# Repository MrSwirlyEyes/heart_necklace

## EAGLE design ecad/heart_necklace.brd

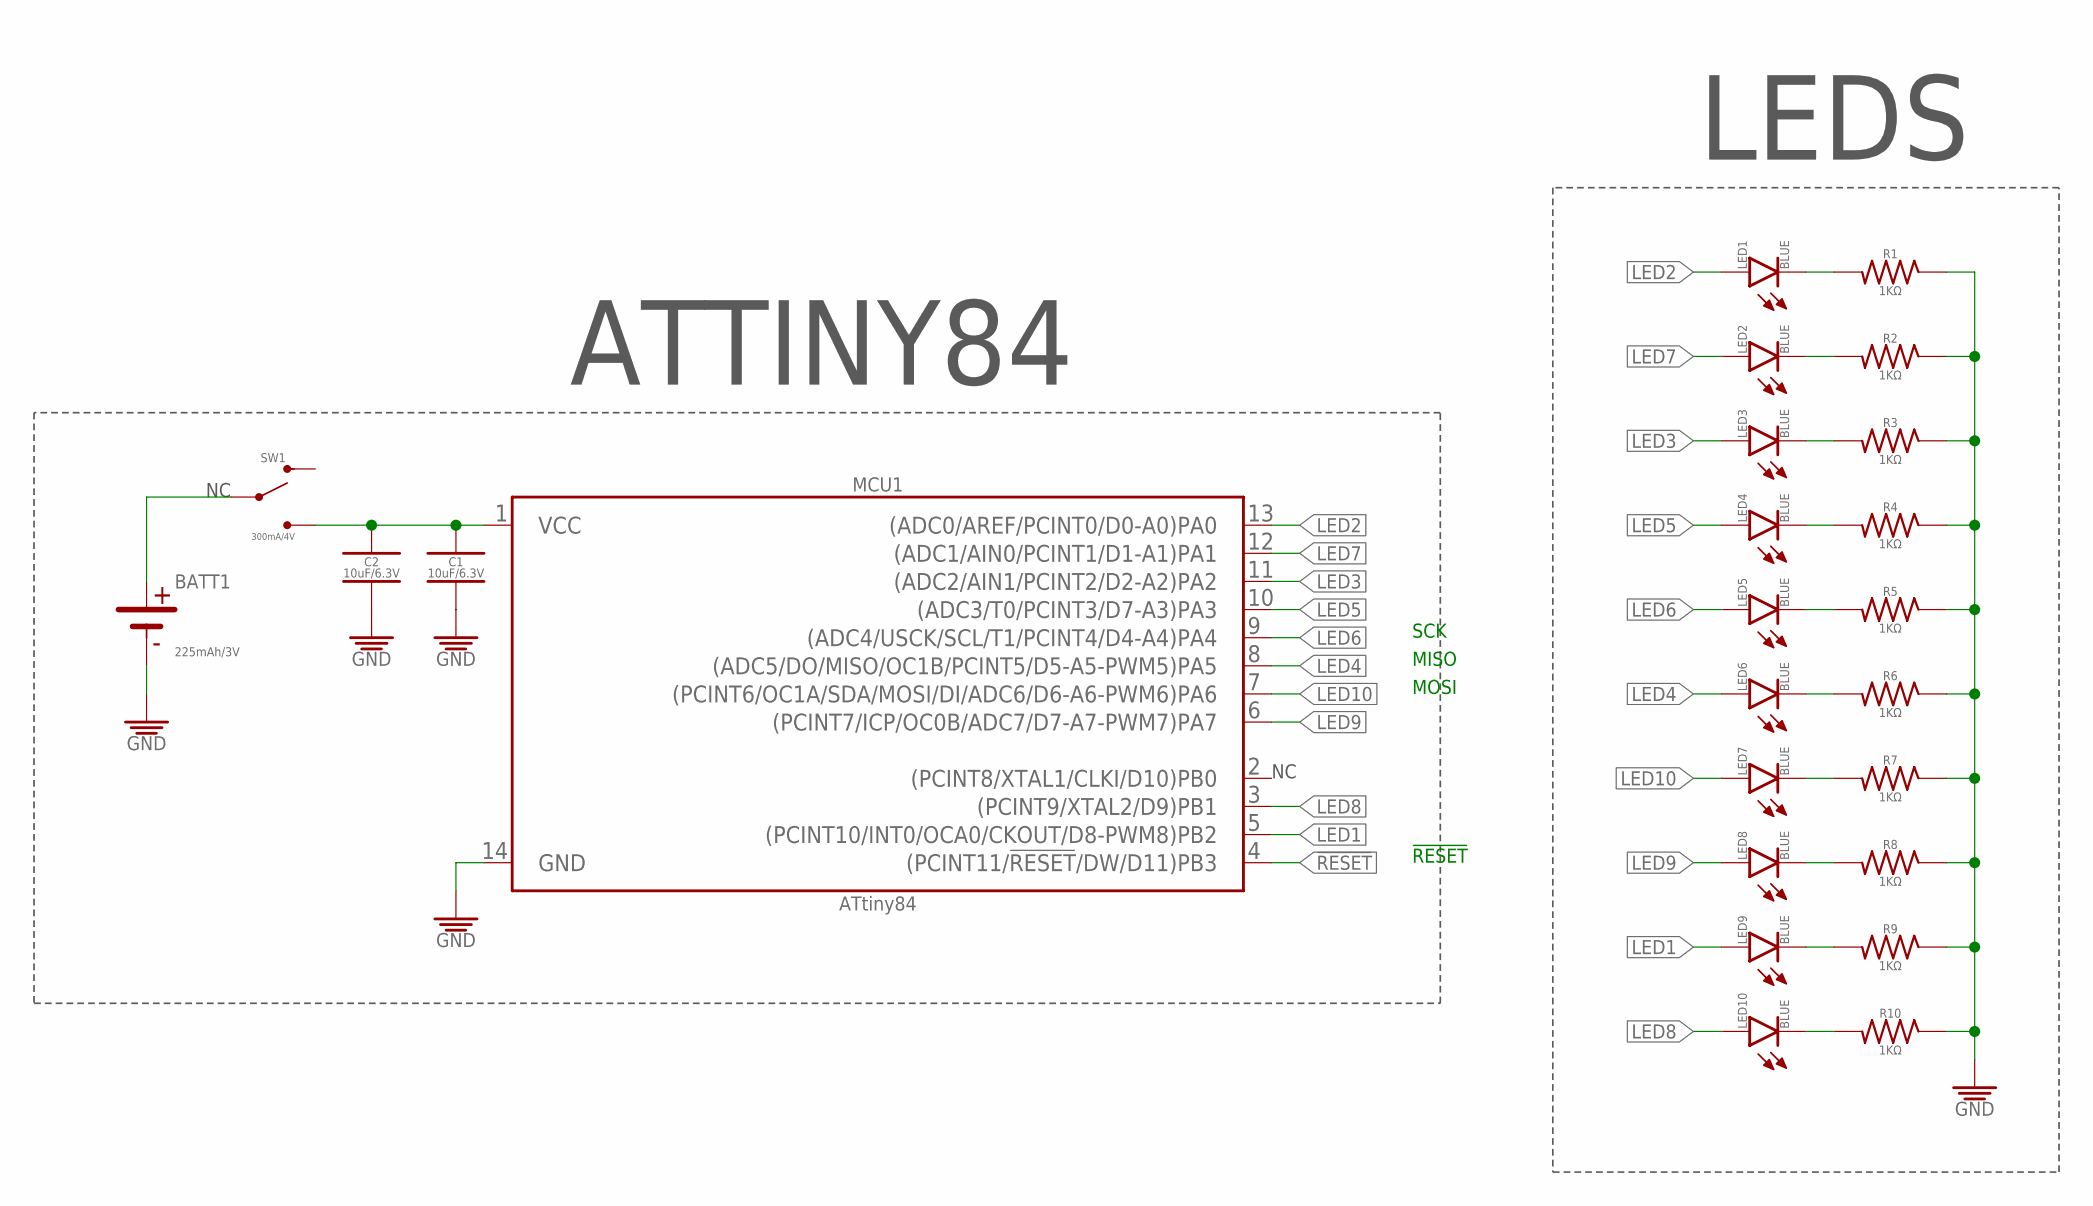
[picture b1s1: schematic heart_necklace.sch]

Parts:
BATT1: 225mAh/3V; CR-2032
C1, C2: 10uF/6.3V; CAPC1005X55_SMD-0402
LED1, LED2, LED3, LED4, LED5, LED6, LED7, LED8, LED9, LED10: BLUE; LEDC2012X120
MCU1: ATtiny84; SOIC127P599X175-14_SOIC-14_NO-SILK
R1, R2, R3, R4, R5, R6, R7, R8, R9, R10: 1KΩ; RESISTOR_SMD-805
SW1: 300mA/4V; SW_SLIDE_SPDT_RA_SMD_4V_300MA_6.7L-2.6W

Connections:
!RESET: MCU1.4 ((PCINT11/!RESET!/DW/D11)PB3)
GND: BATT1.-, C1.2, C2.2, MCU1.14 (GND), R1.1, R2.1, R3.1, R4.1, R5.1, R6.1, R7.1, R8.1, R9.1, R10.1
LED1: LED9.A, MCU1.5 ((PCINT10/INT0/OCA0/CKOUT/D8-PWM8)PB2)
LED2: LED1.A, MCU1.13 ((ADC0/AREF/PCINT0/D0-A0)PA0)
LED3: LED3.A, MCU1.11 ((ADC2/AIN1/PCINT2/D2-A2)PA2)
LED4: LED6.A, MCU1.8 ((ADC5/DO/MISO/OC1B/PCINT5/D5-A5-PWM5)PA5)
LED5: LED4.A, MCU1.10 ((ADC3/T0/PCINT3/D7-A3)PA3)
LED6: LED5.A, MCU1.9 ((ADC4/USCK/SCL/T1/PCINT4/D4-A4)PA4)
LED7: LED2.A, MCU1.12 ((ADC1/AIN0/PCINT1/D1-A1)PA1)
LED8: LED10.A, MCU1.3 ((PCINT9/XTAL2/D9)PB1)
LED9: LED8.A, MCU1.6 ((PCINT7/ICP/OC0B/ADC7/D7-A7-PWM7)PA7)
LED10: LED7.A, MCU1.7 ((PCINT6/OC1A/SDA/MOSI/DI/ADC6/D6-A6-PWM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)
unnamed: LED1.K, R1.2
unnamed: LED2.K, R2.2
unnamed: LED3.K, R3.2
unnamed: LED4.K, R4.2
unnamed: LED5.K, R5.2
unnamed: LED6.K, R6.2
unnamed: LED7.K, R7.2
unnamed: LED8.K, R8.2
unnamed: LED10.K, R10.2
unnamed: LED9.K, R9.2
unnamed: C1.1, C2.1, MCU1.1 (VCC), SW1.3 (S2)
VBATT: BATT1.+_1 (+), BATT1.+_2 (+), SW1.2

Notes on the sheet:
LEDS
ATTINY84
SCK
MISO
MOSI
!RESET

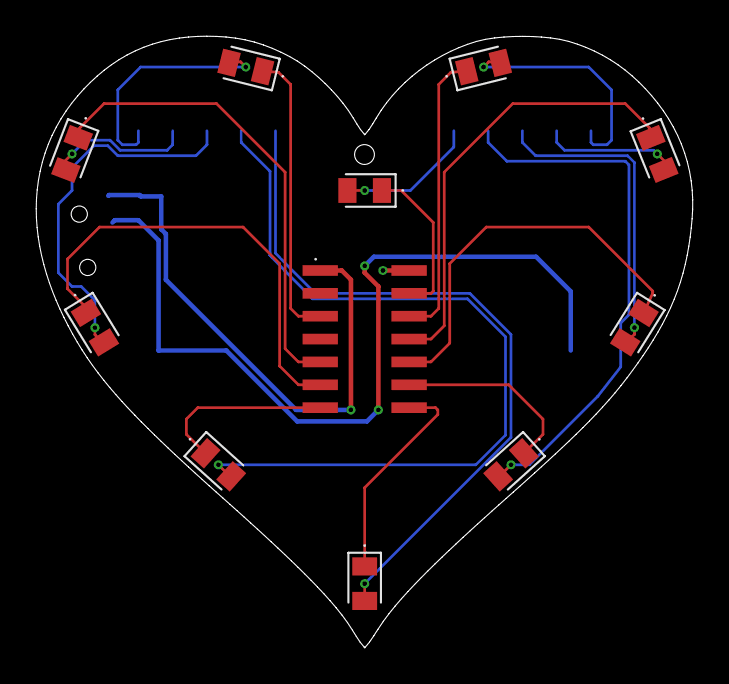
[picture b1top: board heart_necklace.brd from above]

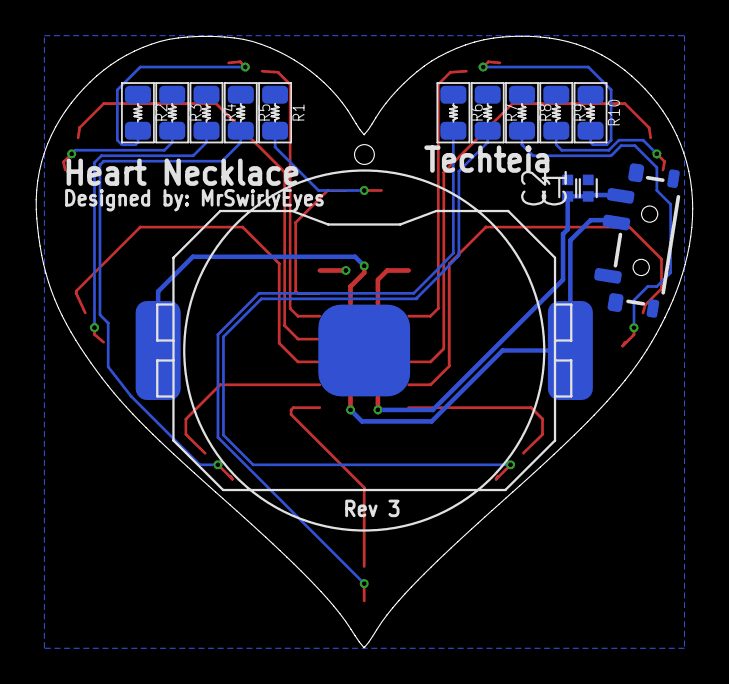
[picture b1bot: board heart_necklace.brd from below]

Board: 2 copper layers, 36.5 x 34.0 mm, 25 parts (14 on the bottom side), 23 nets.

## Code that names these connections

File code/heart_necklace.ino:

//Heart CKT LED Lightshow on ATTiny84

//Note these LED values will need to be
//  changed according to LED Mapping program
#define led1 10
#define led2 9
#define led3 8
#define led4 7
#define led5 6
#define led6 5
#define led7 4
#define led8 3
#define led9 2
#define led10 1

int led[] = { 
              led1, led2, led3, led4, led5,
              led6, led7, led8, led9, led10
            };

//Number of LEDs
int leds = 10;

//Delay variable
unsigned int t = 150;

void setup() {
  //Configuring all LED's to be OUTPUT
  for ( int i = 0 ; i < leds ; i++ ) {
    pinMode(led[i], OUTPUT);
    //digitalWrite(led[i], LOW);
  }
}

//Lightshow sequence
void loop() {

  //All on, forward
  for ( int i = 0 ; i < leds ; i++ ) {
    digitalWrite(led[i], HIGH);
    delay(t);
  }
  //All off, forward
  for ( int i = 0 ; i < leds ; i++ ) {
    digitalWrite(led[i], LOW);
    delay(t);
  }


  //All on, backward
  for ( int i = leds ; i >= 0 ; i-- ) {
    digitalWrite(led[i], HIGH);
    delay(t);
  }
  //All off, backward
  for ( int i = leds ; i >= 0 ; i-- ) {
    digitalWrite(led[i], LOW);
    delay(t);
  }


  //Every even on, backward
  for ( int i = leds ; i >= 0 ; i -= 2 ) {
    digitalWrite(led[i], HIGH);
    delay(t);
  }
  //Every odd on, CCW
  for ( int i = leds - 1 ; i >= 0 ; i -= 2 ) {
    digitalWrite(led[i], HIGH);
    delay(t);
  }
  //First half, off, CW
  for ( int i = 0 ; i <= 5 ; i++ ) {
    digitalWrite(led[i], LOW);
    delay(t);
  }
    //2nd half, off, CCW
  for ( int i = 6 ; i < leds ; i++ ) {
    digitalWrite(led[i], LOW);
    delay(t);
  }

  //First half, on, CCW
  for ( int i = 5 ; i >= 0 ; i-- ) {
    digitalWrite(led[i], HIGH);
    delay(t);
  }
    //2nd half, on, backward
  for ( int i = 6 ; i <= leds ; i++ ) {
    digitalWrite(led[i], HIGH);
    delay(t);
  }

  //First half, off, CW
  for ( int i = 0 ; i <= 5 ; i++ ) {
    digitalWrite(led[i], LOW);
    delay(t);
  }
    //2nd half, on, CCW
  for ( int i = leds ; i >= 6 ; i-- ) {
    digitalWrite(led[i], LOW);
    delay(t);
  }

}

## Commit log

2017-12-18 Started Heart Necklace
2017-12-18 Renamed files to heart_necklace. Added gitignore. Did most of routing
2017-12-19 Almost done with heart necklace
2017-12-19 Rev 1: Heart Necklace complete
2018-03-02 Modify heart necklace
2018-03-02 Move files into folders. Modify gitignore
2018-03-02 Modify gitignore to ignore eagle lock files
2018-06-19 Initialize heart necklace repo?
